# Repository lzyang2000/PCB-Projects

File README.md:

# PCB-Projects
[USB-Charger](USB-Charger/README.md)  
[SPI SD Card Reader](MicroController/README.md)

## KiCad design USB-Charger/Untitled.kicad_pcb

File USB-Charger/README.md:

# USB-Charger
Takes input of 9-18V DC and outputs power compliant with USB Battery Charging 1.2.  
[BOM](https://github.com/lzyang2000/PCB-Projects/blob/master/USB-Charger/USB%20Charger%20BOM.csv)

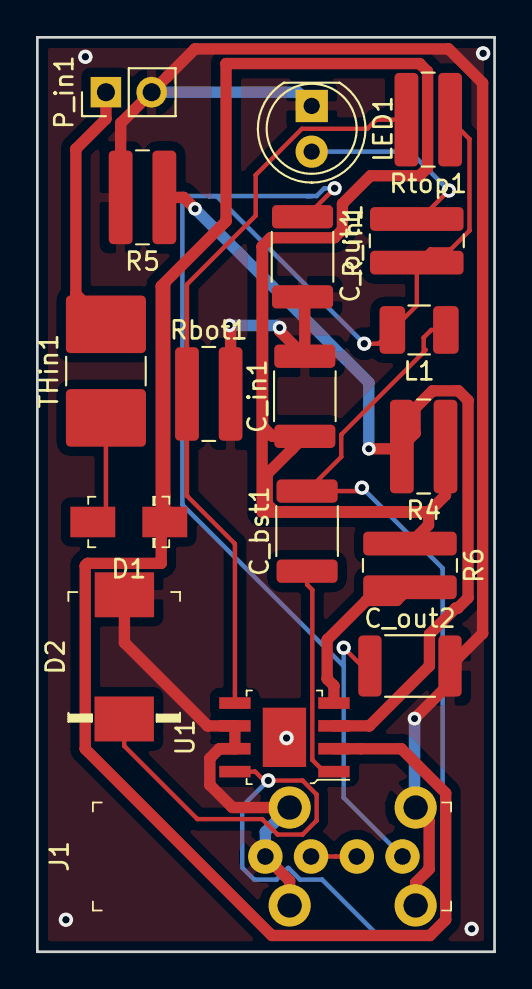
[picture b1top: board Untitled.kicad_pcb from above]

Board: 2 copper layers, 25.4 x 50.8 mm, 18 parts (0 on the bottom side), 12 nets.

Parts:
C_bst1: .1u; C_1812_4532Metric_Pad1.30x3.40mm_HandSolder
C_in1: 10u; C_1812_4532Metric_Pad1.30x3.40mm_HandSolder
C_out1, C_out2: 22u; C_1812_4532Metric_Pad1.30x3.40mm_HandSolder
D1: B240A-13-F; DO-214AC
D2: B560C-13-F; DO-214AB
J1: 73725-0110BLF; USB_A_Female_Vertical_RA_73725-0110BLF
L1: 6.8u; L_1210_3225Metric_Pad1.42x2.65mm_HandSolder
LED1: LED; LED_D5.0mm
P_in1: Conn_01x02_Male; PinHeader_1x02_P2.54mm_Vertical
R4: 56k; R_1020_2550Metric_Pad1.33x5.20mm_HandSolder
R5: 10.2k; R_1020_2550Metric_Pad1.33x5.20mm_HandSolder
R6: 100k; R_1020_2550Metric_Pad1.33x5.20mm_HandSolder
R_in1: 400; R_1020_2550Metric_Pad1.33x5.20mm_HandSolder
Rbot1: 10.2k; R_1020_2550Metric_Pad1.33x5.20mm_HandSolder
Rtop1: 31.5k; R_1020_2550Metric_Pad1.33x5.20mm_HandSolder
THin1: Thermistor_PTC; R_2816_7142Metric_Pad3.20x4.45mm_HandSolder
U1: conv; SOIC-8-1EP_W3.9mm

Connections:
/VIN: C_in1.1, D1.K, R4.1, R6.1, U1.2
/VOUT: C_out1.1, C_out2.1, J1.1, L1.2, R_in1.1, Rtop1.1
GND: C_in1.2, C_out1.2, C_out2.2, D2.A, J1.4, J1.SH, LED1.1, P_in1.2, R5.2, Rbot1.2, U1.6, U1.7
unnamed: C_bst1.1, U1.1
unnamed: C_bst1.2, D2.K, L1.1, U1.8
unnamed: D1.A, THin1.1
unnamed: J1.2, J1.3
unnamed: LED1.2, R_in1.2
unnamed: P_in1.1, THin1.2
unnamed: R4.2, R5.1, U1.3
unnamed: R6.2, U1.4
unnamed: Rbot1.1, Rtop1.2, U1.5

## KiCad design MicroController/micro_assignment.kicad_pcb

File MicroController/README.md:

# SPI SD Card Reader
A basic layout of sd card reader with SPI connection, coupled with IMU

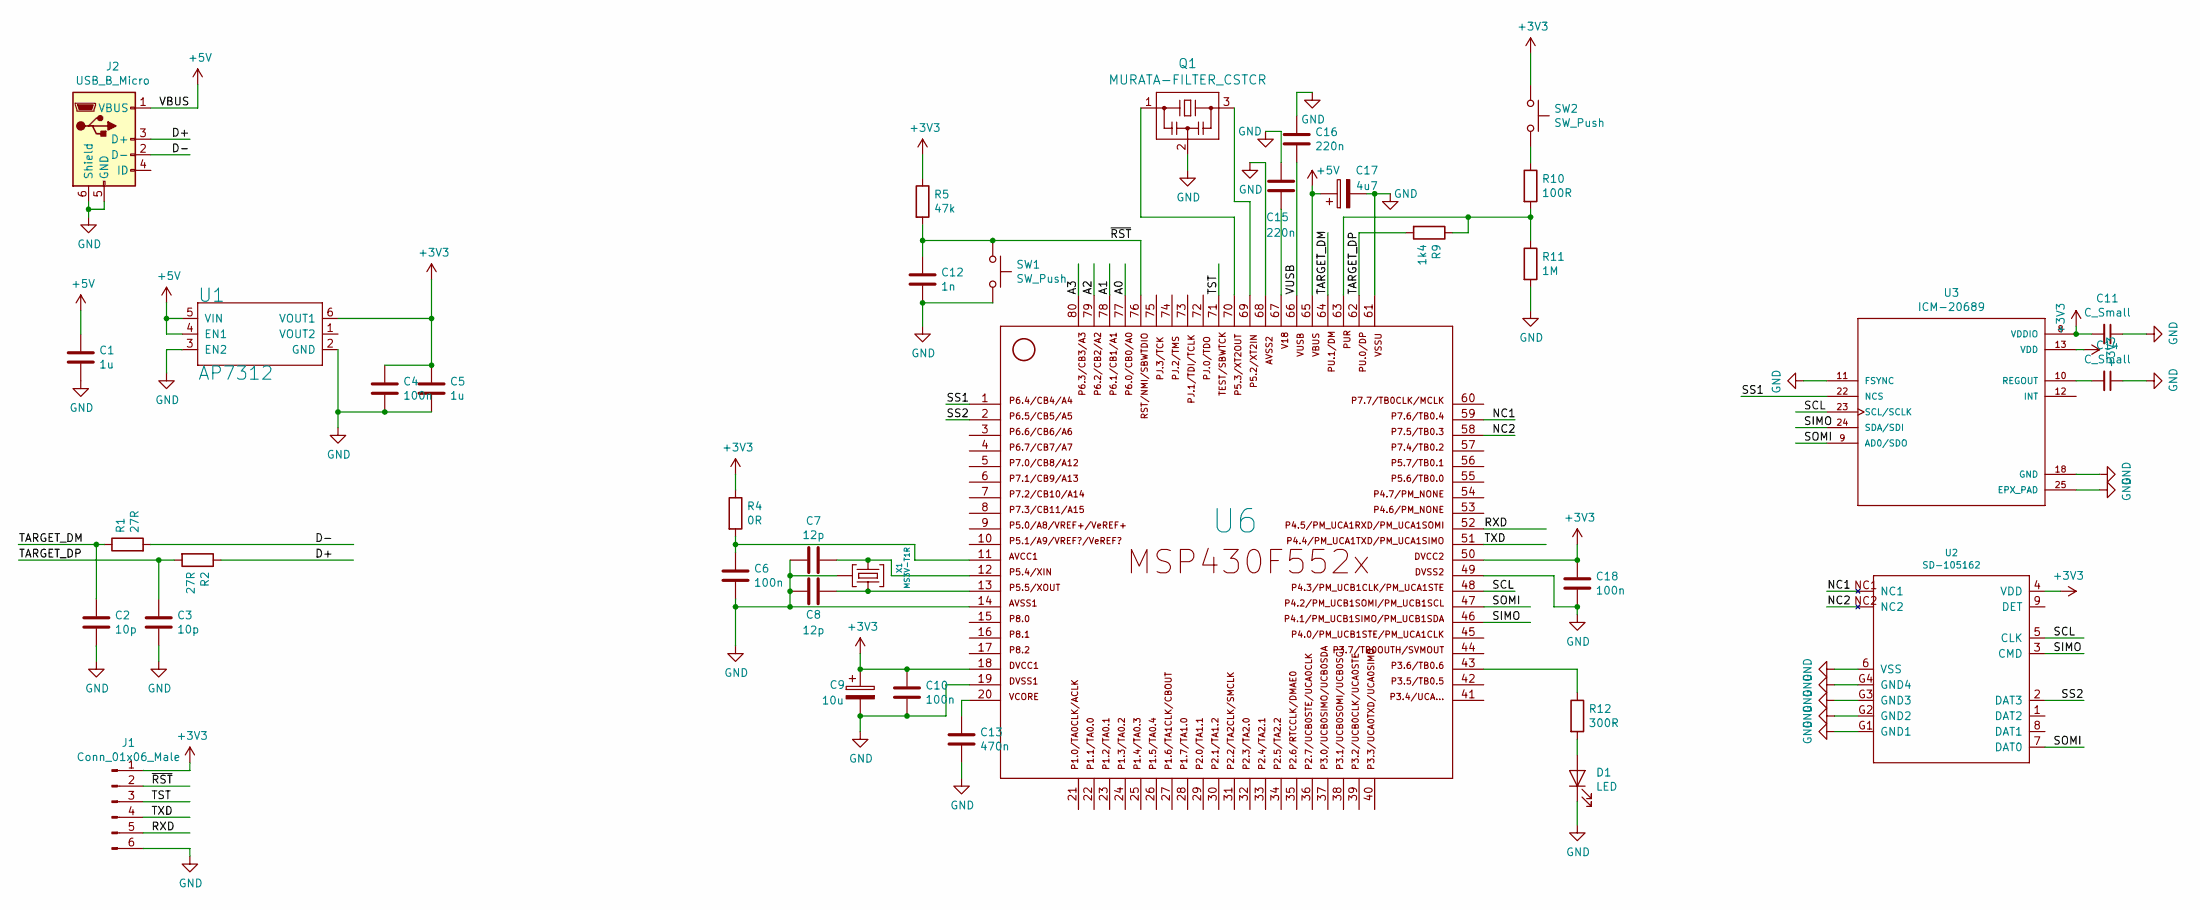
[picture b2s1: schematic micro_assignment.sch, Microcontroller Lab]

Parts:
C1, C5: 1u; C_0805_2012Metric_Pad1.15x1.40mm_HandSolder
C2, C3: 10p; C_0402_1005Metric
C4, C6, C10, C18: 100n; C_0805_2012Metric_Pad1.15x1.40mm_HandSolder
C7, C8: 12p; C_0805_2012Metric_Pad1.15x1.40mm_HandSolder
C9: 10u; 153CLV-0405
C11, C14: C_Small; CP_Elec_3x5.3
C12: 1n; C_0805_2012Metric_Pad1.15x1.40mm_HandSolder
C13: 470n; C_0805_2012Metric_Pad1.15x1.40mm_HandSolder
C15, C16: 220n; C_0805_2012Metric_Pad1.15x1.40mm_HandSolder
C17: 4u7; C_SMD_WURTH_865080540002
D1: LED; LED_0805_2012Metric_Pad1.15x1.40mm_HandSolder
J1: Conn_01x06_Male; PinHeader_1x06_P2.54mm_Vertical
J2: USB_B_Micro; USB_Micro-B_Molex-105017-0001
Q1: MURATA-FILTER_CSTCR; MURATA-CSTCR_G
R1, R2: 27R; R_0402_1005Metric
R4: 0R; R_0805_2012Metric_Pad1.15x1.40mm_HandSolder
R5: 47k; R_0805_2012Metric_Pad1.15x1.40mm_HandSolder
R9: 1k4; R_0805_2012Metric_Pad1.15x1.40mm_HandSolder
R10: 100R; R_0805_2012Metric_Pad1.15x1.40mm_HandSolder
R11: 1M; R_0805_2012Metric_Pad1.15x1.40mm_HandSolder
R12: 300R; R_0805_2012Metric_Pad1.15x1.40mm_HandSolder
SW1, SW2: SW_Push; SW_PUSH_6mm
U1: AP7312; SOT26
U2: SD-105162
U3: ICM-20689; QFN-24-1EP_4x4mm_P0.5mm_EP2.6x2.6mm
U6: F552X---PN80; LQFP-80_12x12mm_P0.5mm
X1: MS3V-T1R

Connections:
+3V3: C4.1, C5.1, C9.1, C10.1, C11.2, C18.1, J1.1, R4.1, R5.1, SW2.1, U1.6 (VOUT1), U2.4 (VDD), U3.8 (VDDIO), U3.13 (VDD), U6.18, U6.50
+5V: C1.1, C17.1, J2.1 (VBUS), U1.4 (EN1), U1.5 (VIN), U6.65
/A0: U6.77
/A1: U6.78
/A2: U6.79
/A3: U6.80
/D+: J2.3 (D+), R2.1
/D-: J2.2 (D-), R1.2
/NC1: U2.NC1, U6.59
/NC2: U2.NC2, U6.58
/RXD: J1.5, U6.52
/SCL: U2.5 (CLK), U3.23 (SCL/SCLK), U6.48
/SIMO: U2.3 (CMD), U3.24 (SDA/SDI), U6.46
/SOMI: U2.7 (DAT0), U3.9 (AD0/SDO), U6.47
/SS1: U3.22 (NCS), U6.1
/SS2: U2.2 (DAT3), U6.2
/TARGET_DM: C2.1, R1.1, U6.64
/TARGET_DP: C3.1, R2.2, R9.2, U6.62
/TST: J1.3, U6.71
/TXD: J1.4, U6.51
/VUSB: C16.2, U6.66
/~RST: C12.1, J1.2, R5.2, SW1.1, U6.76
GND: C1.2, C2.2, C3.2, C4.2, C5.2, C6.2, C7.2, C8.2, C9.2, C10.2, C11.1, C12.2, C13.1, C14.1, C15.1, C16.1, C17.2, C18.2, D1.1 (K), J1.6, J2.5 (GND), J2.6 (Shield), Q1.2, R11.2, SW1.2, U1.2 (GND), U1.3 (EN2), U2.6 (VSS), U2.G1 (GND1), U2.G2 (GND2), U2.G3 (GND3), U2.G4 (GND4), U3.11 (FSYNC), U3.18 (GND), U3.25 (EPX_PAD), U6.14, U6.19, U6.49, U6.61, U6.68, X1.3 (GND)
unnamed: C6.1, R4.2, U6.11
unnamed: C7.1, U6.12, X1.2
unnamed: C8.1, U6.13, X1.1
unnamed: C13.2, U6.20
unnamed: C14.2, U3.10 (REGOUT)
unnamed: C15.2, U6.67
unnamed: D1.2 (A), R12.2
unnamed: Q1.1, U6.70
unnamed: Q1.3, U6.69
unnamed: R10.1, SW2.2
unnamed: R9.1, R10.2, R11.1, U6.63
unnamed: R12.1, U6.43

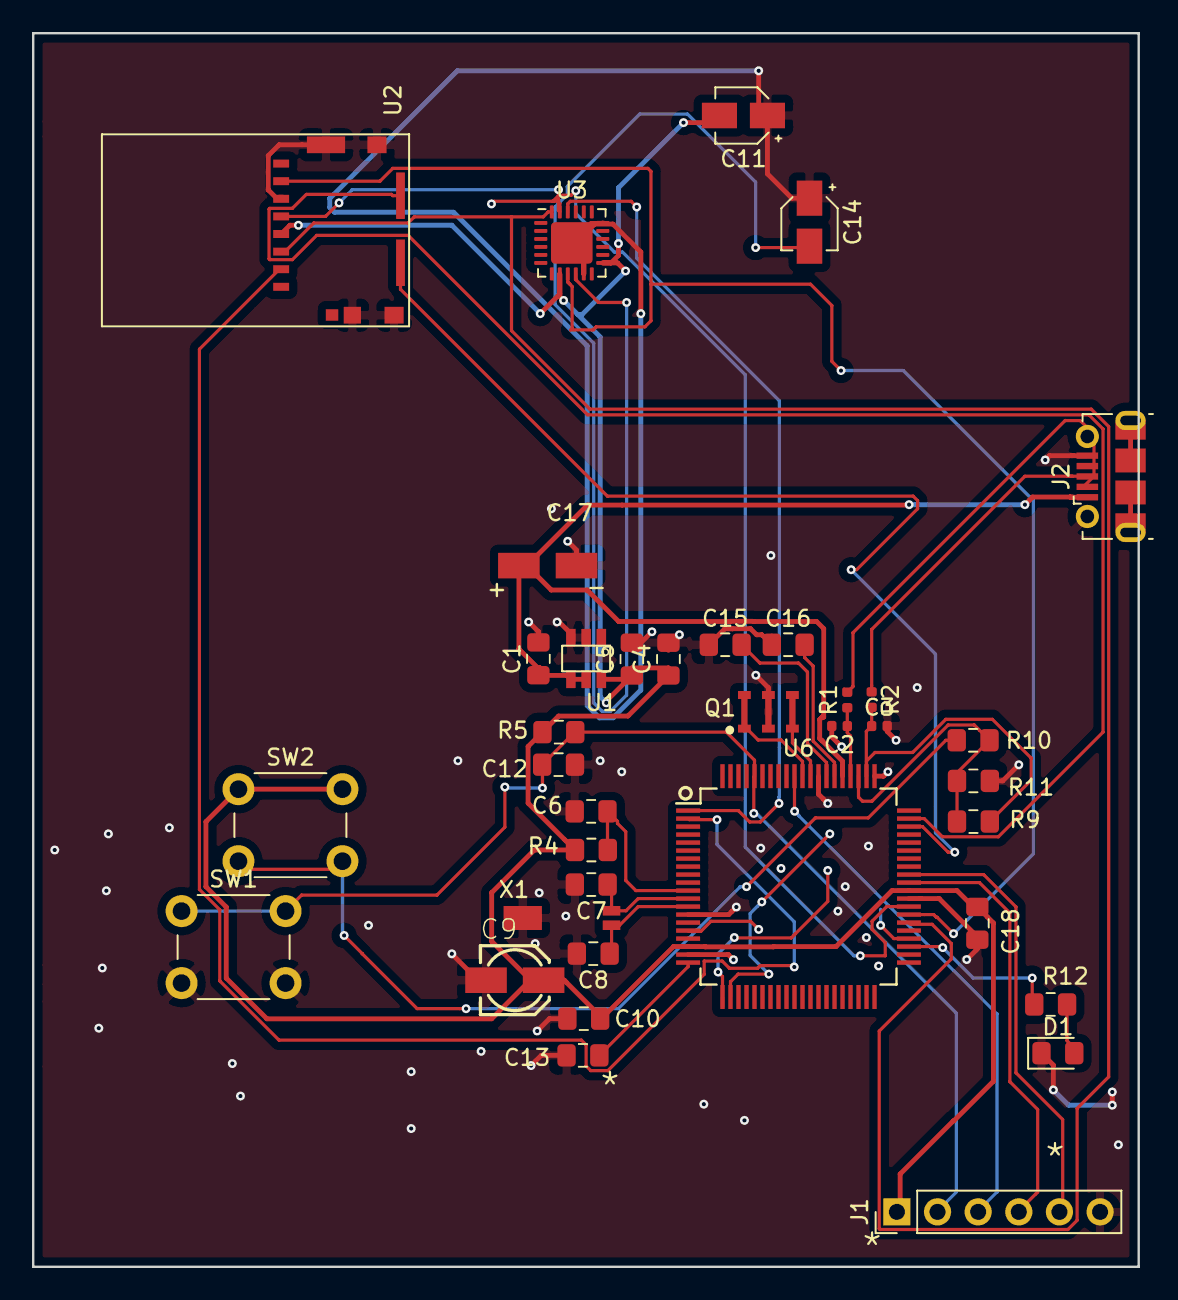
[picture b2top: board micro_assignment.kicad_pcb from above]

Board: 2 copper layers, 69.1 x 77.1 mm, 37 parts (0 on the bottom side), 31 nets.

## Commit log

2019-03-06 USB-Charger
2019-03-06 add readme
2019-03-28 update projects
2019-03-28 update README for SPI SD Card Reader
2019-03-28 update main README
2019-04-11 puff
2019-04-19 lalala
